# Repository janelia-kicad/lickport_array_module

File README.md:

- [Repository Information](#org93a5622)
  - [Description](#orged12863)
- [Images](#org59f66be)
- [Schematic](#orgd93c328)
- [Gerbers](#org90a0575)
- [Bill of Materials](#orgd16dace)
  - [PCB Parts](#orgd11a3c7)
  - [Supplemental Parts](#org13bd6c5)
  - [Vendor Parts Lists](#org316a3d6)
- [Supplemental Documentation](#org85c2034)
  - [Assembly Instructions](#org5e0da59)
- [Manufacturing Archive](#org990f72b)

# Repository Information

-   **Name:** lickport\_array\_module
-   **Version:** 1.1
-   **License:** Open-Source Hardware
-   **URL:** <https://github.com/janelia-kicad/lickport_array_module>
-   **Author:** Peter Polidoro
-   **Email:** peter@polidoro.io

## Description

This module board connects lick sensors and dispense actuators to an array of lickports. A set of these module boards will be assembled into a larger array.

# Images

# Schematic

[./schematic/lickport\_array\_module.pdf](./schematic/lickport_array_module.pdf)

# Gerbers

# Bill of Materials

## PCB Parts

| Item | Reference(s)                                                                                                            | Quantity | Manufacturer                    | Manufacturer Part Number | Vendor   | Vendor Part Number   | Description                                 | Package            |
|---- |----------------------------------------------------------------------------------------------------------------------- |-------- |------------------------------- |------------------------ |-------- |-------------------- |------------------------------------------- |------------------ |
| 1    | C1                                                                                                                      | 1        | Taiyo Yuden                     | GMK212BBJ106MG-T         | Digi-Key | 587-4894-1-ND        | CAP CER 10UF 35V X5R                        | 0805 (2012 Metric) |
| 2    | C10 C12 C14 C16 C18 C20 C22 C24 C26 C4 C6 C8 C2                                                                         | 13       | Vishay Sprague                  | 298D105X0016K2T          | Digi-Key | 718-1618-1-ND        | CAP TANT 1UF 20% 16V                        | 0402               |
| 3    | C11 C13 C15 C17 C19 C21 C23 C25 C27 C5 C7 C9                                                                            | 12       | Murata Electronics              | GRM155R71H473KE14D       | Digi-Key | 490-10702-1-ND       | CAP CER 0.047UF 50V X7R 0402                | 0402               |
| 4    | C3                                                                                                                      | 1        | Yageo                           | CC0402ZRY5V8BB104        | Digi-Key | 311-1375-1-ND        | CAP CER 0.1UF 25V Y5V                       | 0402               |
| 5    | D1                                                                                                                      | 1        | Nexperia USA Inc.               | PMEG45U10EPDAZ           | Digi-Key | 1727-7645-1-ND       | DIODE SCHOTTKY 45V 10A                      | CFP15              |
| 6    | D10 D12 D14 D16 D18 D20 D22 D24 D26 D4 D6 D8 D2                                                                         | 13       | Diodes Incorporated             | BAS116LPH4-7B            | Digi-Key | BAS116LPH4-7BDICT-ND | DIODE GEN PURP 85V 215MA 2DFN               | 0402               |
| 7    | D11 D13 D15 D17 D19 D21 D23 D25 D3 D5 D7 D9                                                                             | 12       | Comchip Technology              | CDBQR0230L               | Digi-Key | 641-1275-1-ND        | DIODE SCHOTTKY 30V 200MA                    | 0402               |
| 8    | L1 L10 L11 L12 L13 L2 L3 L4 L5 L6 L7 L8 L9                                                                              | 13       | Lite-On Inc.                    | LTST-C170GKT             | Digi-Key | 160-1179-1-ND        | LED GREEN CLEAR SMD                         | 0805 (2012 Metric) |
| 9    | P1                                                                                                                      | 1        | CUI Devices                     | PJ-015BH-SMT-TR          | Digi-Key | CP-015BHPJ-CT-ND     | CONN PWR JACK 2.5X5.5MM SOLDER              |                    |
| 10   | P10 P11 P12 P13 P14 P3 P4 P5 P6 P7 P8 P9                                                                                | 12       | Mill-Max Manufacturing Corp.    | 9837-0-15-80-14-27-10-0  | Digi-Key | ED10170-ND           | Pin Receptacle Connector 0.065in to 0.082in |                    |
| 11   | P2                                                                                                                      | 1        | Amphenol RF                     | 031-5633-1010            | Digi-Key | ARF2116-ND           | CONN BNC JACK STR 50 OHM PCB                |                    |
| 12   | R1 R2 R3 R12 R16 R20 R24 R28 R32 R36 R40 R44 R48 R52 R8                                                                 | 15       | Panasonic Electronic Components | ERJ-PA2F2201X            | Digi-Key | P17226CT-ND          | RES SMD 2.2K OHM 1% 1/5W                    | 0402               |
| 13   | R10 R14 R18 R22 R26 R30 R34 R38 R42 R46 R50 R6                                                                          | 12       | Panasonic Electronic Components | ERJ-2RKF1373X            | Digi-Key | P137KLCT-ND          | RES SMD 137K OHM 1% 1/10W                   | 0402               |
| 14   | R11 R15 R19 R23 R27 R31 R35 R39 R43 R47 R51 R7                                                                          | 12       | Panasonic Electronic Components | ERJ-2RKF2053X            | Digi-Key | P205KLCT-ND          | RES SMD 205K OHM 1% 1/10W 0402              | 0402               |
| 15   | R13 R17 R21 R25 R29 R33 R37 R41 R45 R49 R53 R9                                                                          | 12       | Panasonic Electronic Components | ERJ-PA2F2002X            | Digi-Key | P124454CT-ND         |                                             | 0402               |
| 16   | R4 R5                                                                                                                   | 2        | Panasonic Electronic Components | ERJ-PA2F4702X            | Digi-Key | P17234CT-ND          | RES SMD 47K OHM 1% 1/5W                     | 0402               |
| 17   | T1 T10 T11 T12 T2 T3 T4 T5 T6 T7 T8 T9                                                                                  | 12       | Phoenix Contact                 | 1988956                  | Digi-Key | 277-1779-ND          |                                             |                    |
| 18   | TEENSY1                                                                                                                 | 2        | Sullins Connector Solutions     | PPPC141LFBN-RC           | Digi-Key | S7047-ND             | CONN HDR 14POS 0.1 GOLD PCB                 |                    |
| 19   | U1                                                                                                                      | 1        | Microchip Technology            | AT42QT2120-MMHR          | Digi-Key | AT42QT2120-MMHRCT-ND | IC TOUCH SENSOR 12CH                        | 20-VFQFN           |
| 20   | U10 U11 U12 U13 U2 U3 U4 U5 U6 U7 U8 U9                                                                                 | 12       | Texas Instruments               | DRV103U                  | Digi-Key | 296-11622-ND         | IC LO-SIDE DRIVER PWM 8SOIC                 | 8SOIC              |
|      | FID1 FID2 FID3 FID4 MH1 MH10 MH11 MH12 MH13 MH14 MH2 MH3 MH4 MH5 MH6 MH7 MH8 MH9 S1 S10 S11 S12 S2 S3 S4 S5 S6 S7 S8 S9 | 30       |                                 |                          |          |                      |                                             |                    |

## Supplemental Parts

| Item | Quantity | Manufacturer         | Manufacturer Part Number | Vendor   | Vendor Part Number | Description                      |
|---- |-------- |-------------------- |------------------------ |-------- |------------------ |-------------------------------- |
| 1    | 1        | SparkFun Electronics | DEV-16997                | Digi-Key | 1568-DEV-16997-ND  | TEENSY 4.0 (HEADERS)             |
| 2    | 1        | Qualtek              | 3021077-10               | Digi-Key | Q1225-ND           | USB 2.0 A MALE TO USB 2.0 MICRO  |
| 3    | 1        | CUI Inc.             | SDI65-24-UDC-P6          | Digi-Key | 102-4891-ND        | AC/DC DESKTOP ADAPTER 24V 65W    |
| 4    | 1        | Amphenol RF          | 115101-19-120            | Digi-Key | ACX1790-ND         | CBL ASSY BNC PLUG-PLUG RG58 10FT |
| 5    | 24       | Panduit Corp         | FSD73-8-D                | Digi-Key | 298-10557-ND       | CONN FERRULE DIN 24AWG YELLOW    |

## Vendor Parts Lists

[./bom/Digi-Key\_parts.csv](./bom/Digi-Key_parts.csv)

# Supplemental Documentation

## Assembly Instructions

-   Solder surface mount and through hole components onto the pcb.

# Manufacturing Archive

Send manufacturing zip file to your favorite PCB manufacturer for fabrication.

[./manufacturing/lickport\_array\_module\_v1.1.zip](./manufacturing/lickport_array_module_v1.1.zip)

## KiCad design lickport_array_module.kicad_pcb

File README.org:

# Created 2021-06-25 Fri 14:58
#+OPTIONS: title:nil author:nil email:nil toc:t |:t ^:nil
* Repository Information

- Name :: lickport_array_module
- Version :: 1.1
- License :: Open-Source Hardware
- URL :: https://github.com/janelia-kicad/lickport_array_module
- Author :: Peter Polidoro
- Email :: peter@polidoro.io

** Description

This module board connects lick sensors and dispense actuators to an array of
lickports. A set of these module boards will be assembled into a larger array.

* Images

* Schematic

[[file:./schematic/lickport_array_module.pdf][./schematic/lickport_array_module.pdf]]

[[file:./schematic/images/schematic00.png]]

[[file:./schematic/images/schematic01.png]]

[[file:./schematic/images/schematic02.png]]

[[file:./schematic/images/schematic03.png]]

[[file:./schematic/images/schematic04.png]]

[[file:./schematic/images/schematic05.png]]

[[file:./schematic/images/schematic06.png]]

[[file:./schematic/images/schematic07.png]]

[[file:./schematic/images/schematic08.png]]

[[file:./schematic/images/schematic09.png]]

[[file:./schematic/images/schematic10.png]]

[[file:./schematic/images/schematic11.png]]

[[file:./schematic/images/schematic12.png]]

* Gerbers

[[file:./gerbers/images/gerbers00.png]]

[[file:./gerbers/images/gerbers01.png]]

* Bill of Materials

** PCB Parts

| Item | Reference(s)                                                                                                            | Quantity | Manufacturer                    | Manufacturer Part Number | Vendor   | Vendor Part Number   | Description                                 |            Package |
|------+-------------------------------------------------------------------------------------------------------------------------+----------+---------------------------------+--------------------------+----------+----------------------+---------------------------------------------+--------------------|
|    1 | C1                                                                                                                      |        1 | Taiyo Yuden                     | GMK212BBJ106MG-T         | Digi-Key | 587-4894-1-ND        | CAP CER 10UF 35V X5R                        | 0805 (2012 Metric) |
|    2 | C10 C12 C14 C16 C18 C20 C22 C24 C26 C4 C6 C8 C2                                                                         |       13 | Vishay Sprague                  | 298D105X0016K2T          | Digi-Key | 718-1618-1-ND        | CAP TANT 1UF 20% 16V                        |               0402 |
|    3 | C11 C13 C15 C17 C19 C21 C23 C25 C27 C5 C7 C9                                                                            |       12 | Murata Electronics              | GRM155R71H473KE14D       | Digi-Key | 490-10702-1-ND       | CAP CER 0.047UF 50V X7R 0402                |               0402 |
|    4 | C3                                                                                                                      |        1 | Yageo                           | CC0402ZRY5V8BB104        | Digi-Key | 311-1375-1-ND        | CAP CER 0.1UF 25V Y5V                       |               0402 |
|    5 | D1                                                                                                                      |        1 | Nexperia USA Inc.               | PMEG45U10EPDAZ           | Digi-Key | 1727-7645-1-ND       | DIODE SCHOTTKY 45V 10A                      |              CFP15 |
|    6 | D10 D12 D14 D16 D18 D20 D22 D24 D26 D4 D6 D8 D2                                                                         |       13 | Diodes Incorporated             | BAS116LPH4-7B            | Digi-Key | BAS116LPH4-7BDICT-ND | DIODE GEN PURP 85V 215MA 2DFN               |               0402 |
|    7 | D11 D13 D15 D17 D19 D21 D23 D25 D3 D5 D7 D9                                                                             |       12 | Comchip Technology              | CDBQR0230L               | Digi-Key | 641-1275-1-ND        | DIODE SCHOTTKY 30V 200MA                    |               0402 |
|    8 | L1 L10 L11 L12 L13 L2 L3 L4 L5 L6 L7 L8 L9                                                                              |       13 | Lite-On Inc.                    | LTST-C170GKT             | Digi-Key | 160-1179-1-ND        | LED GREEN CLEAR SMD                         | 0805 (2012 Metric) |
|    9 | P1                                                                                                                      |        1 | CUI Devices                     | PJ-015BH-SMT-TR          | Digi-Key | CP-015BHPJ-CT-ND     | CONN PWR JACK 2.5X5.5MM SOLDER              |                    |
|   10 | P10 P11 P12 P13 P14 P3 P4 P5 P6 P7 P8 P9                                                                                |       12 | Mill-Max Manufacturing Corp.    | 9837-0-15-80-14-27-10-0  | Digi-Key | ED10170-ND           | Pin Receptacle Connector 0.065in to 0.082in |                    |
|   11 | P2                                                                                                                      |        1 | Amphenol RF                     | 031-5633-1010            | Digi-Key | ARF2116-ND           | CONN BNC JACK STR 50 OHM PCB                |                    |
|   12 | R1 R2 R3 R12 R16 R20 R24 R28 R32 R36 R40 R44 R48 R52 R8                                                                 |       15 | Panasonic Electronic Components | ERJ-PA2F2201X            | Digi-Key | P17226CT-ND          | RES SMD 2.2K OHM 1% 1/5W                    |               0402 |
|   13 | R10 R14 R18 R22 R26 R30 R34 R38 R42 R46 R50 R6                                                                          |       12 | Panasonic Electronic Components | ERJ-2RKF1373X            | Digi-Key | P137KLCT-ND          | RES SMD 137K OHM 1% 1/10W                   |               0402 |
|   14 | R11 R15 R19 R23 R27 R31 R35 R39 R43 R47 R51 R7                                                                          |       12 | Panasonic Electronic Components | ERJ-2RKF2053X            | Digi-Key | P205KLCT-ND          | RES SMD 205K OHM 1% 1/10W 0402              |               0402 |
|   15 | R13 R17 R21 R25 R29 R33 R37 R41 R45 R49 R53 R9                                                                          |       12 | Panasonic Electronic Components | ERJ-PA2F2002X            | Digi-Key | P124454CT-ND         |                                             |               0402 |
|   16 | R4 R5                                                                                                                   |        2 | Panasonic Electronic Components | ERJ-PA2F4702X            | Digi-Key | P17234CT-ND          | RES SMD 47K OHM 1% 1/5W                     |               0402 |
|   17 | T1 T10 T11 T12 T2 T3 T4 T5 T6 T7 T8 T9                                                                                  |       12 | Phoenix Contact                 | 1988956                  | Digi-Key | 277-1779-ND          |                                             |                    |
|   18 | TEENSY1                                                                                                                 |        2 | Sullins Connector Solutions     | PPPC141LFBN-RC           | Digi-Key | S7047-ND             | CONN HDR 14POS 0.1 GOLD PCB                 |                    |
|   19 | U1                                                                                                                      |        1 | Microchip Technology            | AT42QT2120-MMHR          | Digi-Key | AT42QT2120-MMHRCT-ND | IC TOUCH SENSOR 12CH                        |           20-VFQFN |
|   20 | U10 U11 U12 U13 U2 U3 U4 U5 U6 U7 U8 U9                                                                                 |       12 | Texas Instruments               | DRV103U                  | Digi-Key | 296-11622-ND         | IC LO-SIDE DRIVER PWM 8SOIC                 |              8SOIC |
|      | FID1 FID2 FID3 FID4 MH1 MH10 MH11 MH12 MH13 MH14 MH2 MH3 MH4 MH5 MH6 MH7 MH8 MH9 S1 S10 S11 S12 S2 S3 S4 S5 S6 S7 S8 S9 |       30 |                                 |                          |          |                      |                                             |                    |

** Supplemental Parts

| Item | Quantity | Manufacturer         | Manufacturer Part Number | Vendor   | Vendor Part Number | Description                      |
|------+----------+----------------------+--------------------------+----------+--------------------+----------------------------------|
|    1 |        1 | SparkFun Electronics | DEV-16997                | Digi-Key | 1568-DEV-16997-ND  | TEENSY 4.0 (HEADERS)             |
|    2 |        1 | Qualtek              | 3021077-10               | Digi-Key | Q1225-ND           | USB 2.0 A MALE TO USB 2.0 MICRO  |
|    3 |        1 | CUI Inc.             | SDI65-24-UDC-P6          | Digi-Key | 102-4891-ND        | AC/DC DESKTOP ADAPTER 24V 65W    |
|    4 |        1 | Amphenol RF          | 115101-19-120            | Digi-Key | ACX1790-ND         | CBL ASSY BNC PLUG-PLUG RG58 10FT |
|    5 |       24 | Panduit Corp         | FSD73-8-D                | Digi-Key | 298-10557-ND       | CONN FERRULE DIN 24AWG YELLOW    |
#+TBLFM: $1=@#-1

** Vendor Parts Lists

[[file:./bom/Digi-Key_parts.csv][./bom/Digi-Key_parts.csv]]

* Supplemental Documentation

** Assembly Instructions

- Solder surface mount and through hole components onto the pcb.

* Manufacturing Archive

Send manufacturing zip file to your favorite PCB manufacturer for fabrication.

[[file:./manufacturing/lickport_array_module_v1.1.zip][./manufacturing/lickport_array_module_v1.1.zip]]

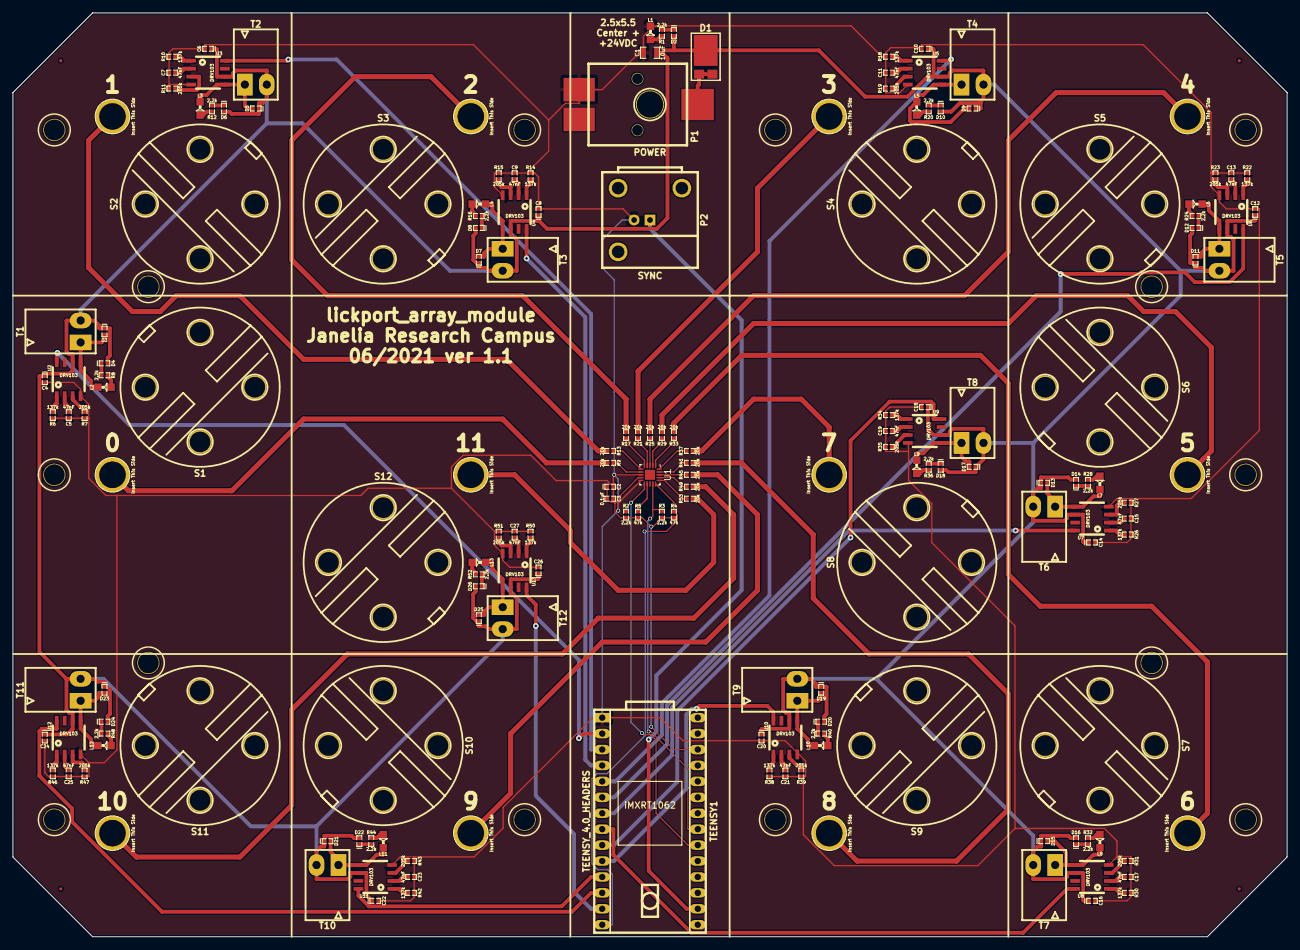
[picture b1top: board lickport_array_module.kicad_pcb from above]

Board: 2 copper layers, 203.2 x 147.3 mm, 189 parts (0 on the bottom side), 119 nets.

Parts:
C1: 10uF; SM0805
C2, C4, C6, C8, C10, C12, C14, C16, C18, C20, C22, C24, C26: 1uF; SM0402_POL
C3: 0.1uF; SM0402
C5, C7, C9, C11, C13, C15, C17, C19, C21, C23, C25, C27: 47nF; SM0402
D1: DIODE_SCHOTTKY_45V_10A; CFP15
D2, D4, D6, D8, D10, D12, D14, D16, D18, D20, D22, D24, D26: DIODE_LOW_REV_CURRENT_0402; SM0402_POL
D3, D5, D7, D9, D11, D13, D15, D17, D19, D21, D23, D25: DIODE_SCHOTTKY_0402; SM0402_POL
FID1, FID2, FID3, FID4: FIDUCIAL
L1, L2, L3, L4, L5, L6, L7, L8, L9, L10, L11, L12, L13: LED_GRN; LED0805
MH1, MH2, MH3, MH4, MH5, MH6, MH7, MH8, MH9, MH10, MH11, MH12, MH13, MH14: MOUNTING_HOLE_4-40
P1: PWR_JACK_2.5x5.5_SMD_VERT; DCJACK_3PIN_SMD_VERT
P2: BNC
P3, P4, P5, P6, P7, P8, P9, P10, P11, P12, P13, P14: RECEPTACLE_2MM
R1, R2, R3, R8, R12, R16, R20, R24, R28, R32, R36, R40, R44, R48, R52: 2.2k; SM0402
R4, R5: 47k; SM0402
R6, R10, R14, R18, R22, R26, R30, R34, R38, R42, R46, R50: 137k; SM0402
R7, R11, R15, R19, R23, R27, R31, R35, R39, R43, R47, R51: 205k; SM0402
R9, R13, R17, R21, R25, R29, R33, R37, R41, R45, R49, R53: 20k; SM0402
S1, S2, S3, S4, S5, S6, S7, S8, S9, S10, S11, S12: CLIPPARD-NPV2-1C-23-24; CLIPPARD_NPV2-1C-23-24
T1, T2, T3, T4, T5, T6, T7, T8, T9, T10, T11, T12: TERM_BLK_ANG_2_PIN_3.5MM_PITCH
TEENSY1: TEENSY_4.0_HEADERS
U1: AT42QT2120-MMHR; QFN-20-1EP_3x3mm_P0.45mm_EP1.6x1.6mm
U2, U3, U4, U5, U6, U7, U8, U9, U10, U11, U12, U13: DRV103; SOIC_8

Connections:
/RESET: R5.2, U1.12
/SCL: R3.2, TEENSY1.19, U1.14
/SDA: R2.2, TEENSY1.18, U1.11
/SOLENOID_0: TEENSY1.0, U2.8
/SOLENOID_1: TEENSY1.1, U3.8
/SOLENOID_2: TEENSY1.2, U4.8
/SOLENOID_3: TEENSY1.3, U5.8
/SOLENOID_4: TEENSY1.4, U6.8
/SOLENOID_5: TEENSY1.5, U7.8
/SOLENOID_6: TEENSY1.6, U8.8
/SOLENOID_7: TEENSY1.7, U9.8
/SOLENOID_8: TEENSY1.8, U10.8
/SOLENOID_9: TEENSY1.9, U11.8
/SOLENOID_10: TEENSY1.10, U12.8
/SOLENOID_11: TEENSY1.11, U13.8
/SYNC: P2.1, TEENSY1.14
/TOUCH_0: R9.2, U1.7
/TOUCH_1: R13.2, U1.6
/TOUCH_2: R17.2, U1.5
/TOUCH_3: R21.2, U1.4
/TOUCH_4: R25.2, U1.3
/TOUCH_5: R29.2, U1.2
/TOUCH_6: R33.2, U1.1
/TOUCH_7: R37.2, U1.20
/TOUCH_8: R41.2, U1.19
/TOUCH_9: R45.2, U1.18
/TOUCH_10: R49.2, U1.17
/TOUCH_11: R53.2, U1.16
/lickport_interface_0/SENSE: P3.1, R9.1
/lickport_interface_0/SH: D3.2, L2.2, T1.1, U2.5
/lickport_interface_1/SENSE: P4.1, R13.1
/lickport_interface_1/SH: D5.2, L3.2, T2.1, U3.5
/lickport_interface_2/SENSE: P5.1, R17.1
/lickport_interface_2/SH: D7.2, L4.2, T3.1, U4.5
/lickport_interface_3/SENSE: P6.1, R21.1
/lickport_interface_3/SH: D9.2, L5.2, T4.1, U5.5
/lickport_interface_4/SENSE: P7.1, R25.1
/lickport_interface_4/SH: D11.2, L6.2, T5.1, U6.5
/lickport_interface_5/SENSE: P8.1, R29.1
/lickport_interface_5/SH: D13.2, L7.2, T6.1, U7.5
/lickport_interface_6/SENSE: P9.1, R33.1
/lickport_interface_6/SH: D15.2, L8.2, T7.1, U8.5
/lickport_interface_7/SENSE: P10.1, R37.1
/lickport_interface_7/SH: D17.2, L9.2, T8.1, U9.5
/lickport_interface_8/SENSE: P11.1, R41.1
/lickport_interface_8/SH: D19.2, L10.2, T9.1, U10.5
/lickport_interface_9/SENSE: P12.1, R45.1
/lickport_interface_9/SH: D21.2, L11.2, T10.1, U11.5
/lickport_interface_10/SENSE: P13.1, R49.1
/lickport_interface_10/SH: D23.2, L12.2, T11.1, U12.5
/lickport_interface_11/SENSE: P14.1, R53.1
/lickport_interface_11/SH: D25.2, L13.2, T12.1, U13.5
/~CHANGE: R4.2, TEENSY1.12, U1.15
GND: C1.2, C2.2, C3.2, C4.2, C5.2, C6.2, C7.2, C8.2, C9.2, C10.2, C11.2, C12.2, C13.2, C14.2, C15.2, C16.2, C17.2, C18.2, C19.2, C20.2, C21.2, C22.2, C23.2, C24.2, C25.2, C26.2, C27.2, L1.2, P1.2, P2.2, R6.2, R7.2, R10.2, R11.2, R14.2, R15.2, R18.2, R19.2, R22.2, R23.2, R26.2, R27.2, R30.2, R31.2, R34.2, R35.2, R38.2, R39.2, R42.2, R43.2, R46.2, R47.2, R50.2, R51.2, TEENSY1.GND, U1.8, U1.10, U2.4, U3.4, U4.4, U5.4, U6.4, U7.4, U8.4, U9.4, U10.4, U11.4, U12.4, U13.4
unnamed: C5.1, U2.2
unnamed: C7.1, U3.2
unnamed: C9.1, U4.2
unnamed: C11.1, U5.2
unnamed: C13.1, U6.2
unnamed: C15.1, U7.2
unnamed: C17.1, U8.2
unnamed: C19.1, U9.2
unnamed: C21.1, U10.2
unnamed: C23.1, U11.2
unnamed: C25.1, U12.2
unnamed: C27.1, U13.2
unnamed: D2.1, R1.1
unnamed: D4.1, R8.1
unnamed: D6.1, R12.1
unnamed: D8.1, R16.1
unnamed: D10.1, R20.1
unnamed: D12.1, R24.1
unnamed: D14.1, R28.1
unnamed: D16.1, R32.1
unnamed: D18.1, R36.1
unnamed: D20.1, R40.1
unnamed: D22.1, R44.1
unnamed: D24.1, R48.1
unnamed: D26.1, R52.1
unnamed: L1.1, R1.2
unnamed: L2.1, R8.2
unnamed: L3.1, R12.2
unnamed: L4.1, R16.2
unnamed: L5.1, R20.2
unnamed: L6.1, R24.2
unnamed: L7.1, R28.2
unnamed: L8.1, R32.2
unnamed: L9.1, R36.2
unnamed: L10.1, R40.2
unnamed: L11.1, R44.2
unnamed: L12.1, R48.2
unnamed: L13.1, R52.2
unnamed: R6.1, U2.1
unnamed: R7.1, U2.3
unnamed: R10.1, U3.1
unnamed: R11.1, U3.3
unnamed: R14.1, U4.1
unnamed: R15.1, U4.3
unnamed: R18.1, U5.1
unnamed: R19.1, U5.3
unnamed: R22.1, U6.1
unnamed: R23.1, U6.3
unnamed: R26.1, U7.1
unnamed: R27.1, U7.3
unnamed: R30.1, U8.1
unnamed: R31.1, U8.3
unnamed: R34.1, U9.1
unnamed: R35.1, U9.3
unnamed: R38.1, U10.1
unnamed: R39.1, U10.3
unnamed: R42.1, U11.1
unnamed: R43.1, U11.3
unnamed: R46.1, U12.1
unnamed: R47.1, U12.3
unnamed: R50.1, U13.1
unnamed: R51.1, U13.3
VAA: D1.2, P1.1
VCC: C1.1, C4.1, C6.1, C8.1, C10.1, C12.1, C14.1, C16.1, C18.1, C20.1, C22.1, C24.1, C26.1, D1.1, D2.2, D3.1, D4.2, D5.1, D6.2, D7.1, D8.2, D9.1, D10.2, D11.1, D12.2, D13.1, D14.2, D15.1, D16.2, D17.1, D18.2, D19.1, D20.2, D21.1, D22.2, D23.1, D24.2, D25.1, D26.2, T1.2, T2.2, T3.2, T4.2, T5.2, T6.2, T7.2, T8.2, T9.2, T10.2, T11.2, T12.2, U2.6, U3.6, U4.6, U5.6, U6.6, U7.6, U8.6, U9.6, U10.6, U11.6, U12.6, U13.6
VDD: C2.1, C3.1, R2.1, R3.1, R4.1, R5.1, TEENSY1.3V3, U1.9

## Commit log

2021-05-27 Add local power
2021-05-27 Update version numbers
2021-06-01 solenoid_spike_hold -> lickport_interface
2021-06-01 TEENSY_4.0 -> TEENSY_4.1
2021-06-02 Tune DRV103 to solenoid
2021-06-02 Add some components and footprints
2021-06-07 Add touch sensor
2021-06-07 Add assembly images
2021-06-07 Add construction dxf to pcb
2021-06-08 Add pin receptacle
2021-06-09 Add resistors
2021-06-10 Separate solenoid from electrical connector
2021-06-11 Start layout
2021-06-14 Lay out solenoids
2021-06-15 Switch Teensy connection from pin receptacles to headers
2021-06-15 Completed initial layout
2021-06-15 Initial routing
2021-06-16 Add moisture tolerant datasheet
2021-06-16 Switch from Teensy 4.1 to Teensy 4.0 and hand route sense tracks
2021-06-16 Update net classes
2021-06-16 Modify net classes
2021-06-16 Final layout before exporting files
2021-06-17 Generate documentation
2021-06-18 Update ferrule size
2021-06-23 Update bom
2021-06-25 Update components to find make sure all are in stock
2021-09-16 Update email address
2021-09-17 Update generate_kicad_documentation
2021-09-21 Remove ignored files
2022-02-22 Add guix files
2022-02-23 Add guix documentation
